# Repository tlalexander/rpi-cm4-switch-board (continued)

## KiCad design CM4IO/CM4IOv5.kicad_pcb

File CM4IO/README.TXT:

These files have been created in prerelease version 6 of KiCAD. If Version 6 isn't released yet then to use them you will need to download a nightly build of KiCAD. NB Nightly builds my have issues so please check the issue tracker. 

Some of the 3d models need to be downloaded form the following places and put into the CM4IO.3shapes directory some models are approximations.

https://datasheets.raspberrypi.org/cm4/CM4-step.zip
https://www.amphenol-icc.com/pci-express-1001878311200tlf.html
https://www.te.com/global-en/product-171826-4.html
https://www.molex.com/molex/products/part-detail/memory_card_socket/5033981892

The models provided in the 3dmodels directory are from various manufacturers including Diodes, Hirose, MTCONN,Toby, TRXCOM. Terms and conditions for the use of the models remain with the original manufacture.

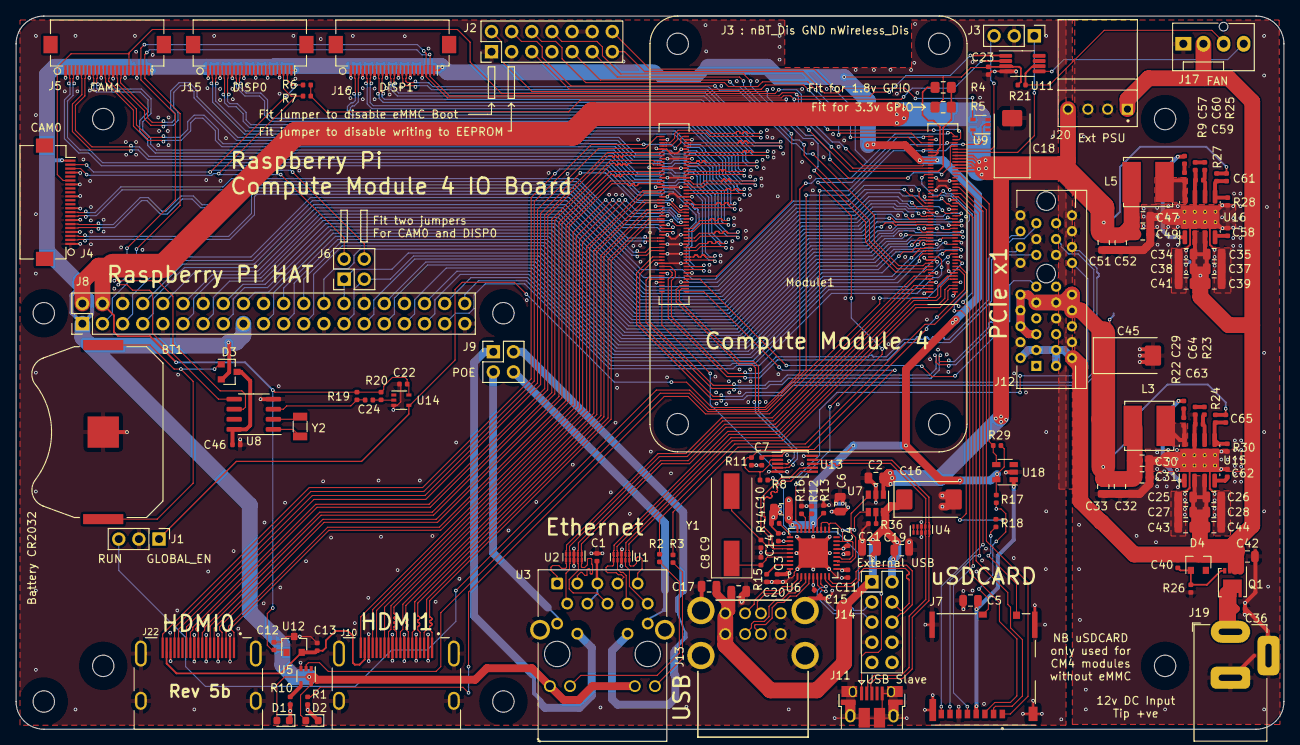
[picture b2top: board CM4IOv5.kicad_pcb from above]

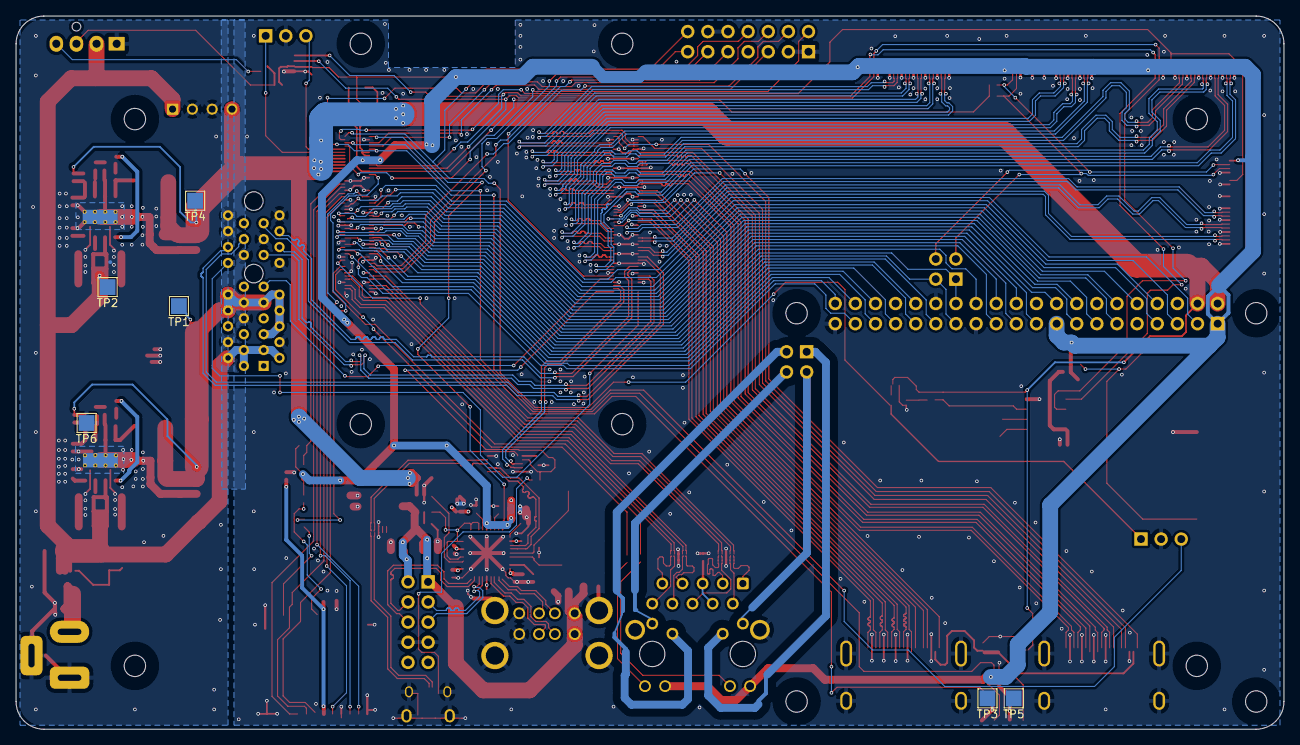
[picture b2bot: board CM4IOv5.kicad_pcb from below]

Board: 4 copper layers, 160.0 x 90.0 mm, 151 parts (6 on the bottom side), 204 nets.

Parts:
BT1: Battery_Cell; BatteryHolder_Keystone_3034_1x20mm
C1, C3, C4, C7, C11, C12, C13, C14, C15, C22, C23, C24, C29, C40, C46, C57, C58, C62: 100n; C_0402_1005Metric
C2, C5, C6, C10, C17, C19, C20, C21, C30, C31, C32, C33, C47, C49, C51, C52: 10u; C_0805_2012Metric
C8, C9: 27pF; C_0402_1005Metric
C16, C18, C45: 100uF; CP_EIA-7343-31_Kemet-D
C25, C26, C27, C28, C34, C35, C37, C38, C39, C41, C42, C43, C44: 10u 35v; C_0805_2012Metric
C36: 100n 100v; C_0402_1005Metric
C59, C61, C63, C65: nf; C_0402_1005Metric
C60, C64: 1.2nF; C_0402_1005Metric
D1: LED Red; LED_0603_1608Metric
D2: LED Green; LED_0603_1608Metric
D3: BAT54C-7-F; SOT-23
D4: MMBZ5242BLT3G; D_SOT-23_ANK
H1, H2, H3, H4, H5, H6, H7, H8: MountingHole; MountingHole_2.7mm_M2.5
J1, J3: Conn_01x03; PinHeader_1x03_P2.54mm_Vertical
J2: Conn_02x07_Odd_Even; PinHeader_2x07_P2.54mm_Vertical
J4, J5, J15, J16: Conn_01x22_Female; Hirose_FH12-22S-0.5SH_1x22-1MP_P0.50mm_Horizontal
J6, J9: THD-02-R; PinHeader_2x02_P2.54mm_Vertical
J7: Micro_SD_Card_Det; SDCARD_MOLEX_503398-1892
J8: THD-20-R; PinHeader_2x20_P2.54mm_Vertical
J10, J22: 690-019-298-412; EDAC 690-019-298-412
J11: USB_OTG; USB_Micro-B_EDAC_UCON00686
J12: 10018783-11200TLF; PCIex1-36
J13: 690-008-221-904; MOLEX_USB_67298-4090
J14: Conn_02x05_Odd_Even; PinHeader_2x05_P2.54mm_Vertical
J17: Molex 470531000; FanPinHeader_1x04_P2.54mm_Vertical
J19: Barrel_Jack; BarrelJack_Horizontal
J20: AMP171826-4; TE_171826-4
L3, L5: SRN6045TA-3R3Y; L_Bourns_SRN6045TA
Module1: ComputeModule4; Raspberry-Pi-4-Compute-Module
Q1: DMP3013SFV-7; Diodes_PowerDI3333-8
R1, R10: 1k; R_0402_1005Metric
R2, R3: 470R; R_0402_1005Metric
R4: nf; R_0805_2012Metric_Pad1.15x1.40mm_HandSolder
R5: 0R; R_0805_2012Metric_Pad1.15x1.40mm_HandSolder
R6, R7, R8, R11, R28: 2.2K 1%; R_0402_1005Metric
R9, R22: 10R; R_0402_1005Metric
R12, R13, R14, R16, R21: 36K 1%; R_0402_1005Metric
R15, R23, R26, R27, R29: 12K 1%; R_0402_1005Metric
R17, R18: nf; R_0402_1005Metric
R19, R20: 510K 1%; R_0402_1005Metric
R24: 47K 1%; R_0402_1005Metric
R25: 20K 1%; R_0402_1005Metric
R30, R36: 15K 1%; R_0402_1005Metric
TP1, TP2, TP3, TP4, TP5, TP6: TestPoint; TestPoint_Pad_2.0x2.0mm
U1, U2, U4: TPD4EUSB30; USON-10_2.5x1.0mm_P0.5mm
U3: MagJack-A70-112-331N126; TRJG0926HENL
U5, U9, U14: 74LVC1G07SE-7; SOT-353_SC-70-5
U6: USB2514B-I/M2; QFN-36-1EP_6x6mm_P0.5mm_EP3.7x3.7mm
U7: AP22653W6; SOT-23-6
U8: PCF85063AT/AAZ; SOIC-8_3.9x4.9mm_P1.27mm
U11: EMC2301-1-ACZL-TR; MSOP-8_3x3mm_P0.65mm
U12: RT9742SNGV; SOT-23
U13: FSUSB42MUX; MSOP-10_3x3mm_P0.5mm
U15, U16: AP64501SP-13; SOIC-8-1EP_3.9x4.9mm_P1.27mm_EP2.95x4.9mm_Mask2.71x3.4mm_Th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
U18: RT9742GGJ5; SOT-23-5
Y1: 24MHz; Crystal_SMD_HC49-SD
Y2: X32K768S301; Crystal_SMD_3215-2Pin_3.2x1.5mm

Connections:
/+3.3v: C3.1, C4.1, C6.1, C7.1, C10.1, C11.1, C14.1, C15.1, C23.1, D1.2 (A), D2.2 (A), D3.2, J4.22, J5.22, J8.1, J8.17, J15.22, J16.22, Module1.84 (+3.3v_(Output)), Module1.86 (+3.3v_(Output)), R5.1, R17.1, R21.2, R29.1, U3.15 (LEDG_A), U3.17 (LEDY_A), U5.5 (VCC), U6.5 (VDDA33), U6.10 (VDDA33), U6.15 (VDD33), U6.23 (VDD33), U6.27 (VBUS_DET), U6.29 (VDDA33), U6.36 (VDDA33), U11.3 (VDD), U13.1 (VCC), U18.5 (IN)
/+5v: C2.1, C12.1, C18.1, C22.1, C47.1, C49.1, C51.1, C52.1, C61.1, J8.2, J8.4, J20.4, L5.2, Module1.77 (+5v_(Input)), Module1.79 (+5v_(Input)), Module1.81 (+5v_(Input)), Module1.83 (+5v_(Input)), Module1.85 (+5v_(Input)), Module1.87 (+5v_(Input)), R19.2, R20.2, R27.1, TP4.1, U7.1 (IN), U9.5 (VCC), U12.1 (IN), U14.5 (VCC)
/+12v: C25.1, C26.1, C27.1, C28.1, C34.1, C35.1, C37.1, C38.1, C39.1, C40.1, C41.1, C42.1, C43.1, C44.1, D4.1 (K), J12.A2 (+12V), J12.A3 (+12V), J12.B1 (+12v), J12.B2 (+12v), J12.B3 (+12v), J17.2, J20.1, Q1.1 (S), Q1.2 (S), Q1.3 (S), TP2.1, U15.2 (VIN), U15.3 (EN), U16.2 (VIN), U16.3 (EN)
/CAM_GPIO: J4.17, J5.17, Module1.97 (Camera_GPIO)
/CM4_GPIO ( Ethernet, GPIO, SDCARD)/+1.8v: Module1.88 (+1.8v_(Output)), Module1.90 (+1.8v_(Output)), R4.1
/CM4_GPIO ( Ethernet, GPIO, SDCARD)/AIN0: J2.5, Module1.96 (AnalogIP0)
/CM4_GPIO ( Ethernet, GPIO, SDCARD)/AIN1: J2.6, Module1.94 (AnalogIP1)
/CM4_GPIO ( Ethernet, GPIO, SDCARD)/BT_nDis: J3.3, Module1.91 (BT_nDisable)
/CM4_GPIO ( Ethernet, GPIO, SDCARD)/EEPROM_nWP: J2.4, Module1.20 (EEPROM_nWP)
/CM4_GPIO ( Ethernet, GPIO, SDCARD)/ETH_LEDG: Module1.17 (Ethernet_nLED2(3.3v)), R2.2
/CM4_GPIO ( Ethernet, GPIO, SDCARD)/ETH_LEDY: Module1.15 (Ethernet_nLED3(3.3v)), R3.2
/CM4_GPIO ( Ethernet, GPIO, SDCARD)/GPIO2: J8.3, Module1.58 (GPIO2)
/CM4_GPIO ( Ethernet, GPIO, SDCARD)/GPIO3: J8.5, Module1.56 (GPIO3)
/CM4_GPIO ( Ethernet, GPIO, SDCARD)/GPIO4: J8.7, Module1.54 (GPIO4)
/CM4_GPIO ( Ethernet, GPIO, SDCARD)/GPIO5: J8.29, Module1.34 (GPIO5)
/CM4_GPIO ( Ethernet, GPIO, SDCARD)/GPIO6: J8.31, Module1.30 (GPIO6)
/CM4_GPIO ( Ethernet, GPIO, SDCARD)/GPIO7: J8.26, Module1.37 (GPIO7)
/CM4_GPIO ( Ethernet, GPIO, SDCARD)/GPIO8: J8.24, Module1.39 (GPIO8)
/CM4_GPIO ( Ethernet, GPIO, SDCARD)/GPIO9: J8.21, Module1.40 (GPIO9)
/CM4_GPIO ( Ethernet, GPIO, SDCARD)/GPIO10: J8.19, Module1.44 (GPIO10)
/CM4_GPIO ( Ethernet, GPIO, SDCARD)/GPIO11: J8.23, Module1.38 (GPIO11)
/CM4_GPIO ( Ethernet, GPIO, SDCARD)/GPIO12: J8.32, Module1.31 (GPIO12)
/CM4_GPIO ( Ethernet, GPIO, SDCARD)/GPIO13: J8.33, Module1.28 (GPIO13)
/CM4_GPIO ( Ethernet, GPIO, SDCARD)/GPIO14: J8.8, Module1.55 (GPIO14)
/CM4_GPIO ( Ethernet, GPIO, SDCARD)/GPIO15: J8.10, Module1.51 (GPIO15)
/CM4_GPIO ( Ethernet, GPIO, SDCARD)/GPIO16: J8.36, Module1.29 (GPIO16)
/CM4_GPIO ( Ethernet, GPIO, SDCARD)/GPIO17: J8.11, Module1.50 (GPIO17)
/CM4_GPIO ( Ethernet, GPIO, SDCARD)/GPIO18: J8.12, Module1.49 (GPIO18)
/CM4_GPIO ( Ethernet, GPIO, SDCARD)/GPIO19: J8.35, Module1.26 (GPIO19)
/CM4_GPIO ( Ethernet, GPIO, SDCARD)/GPIO20: J8.38, Module1.27 (GPIO20)
/CM4_GPIO ( Ethernet, GPIO, SDCARD)/GPIO21: J8.40, Module1.25 (GPIO21)
/CM4_GPIO ( Ethernet, GPIO, SDCARD)/GPIO22: J8.15, Module1.46 (GPIO22)
/CM4_GPIO ( Ethernet, GPIO, SDCARD)/GPIO23: J8.16, Module1.47 (GPIO23)
/CM4_GPIO ( Ethernet, GPIO, SDCARD)/GPIO24: J8.18, Module1.45 (GPIO24)
/CM4_GPIO ( Ethernet, GPIO, SDCARD)/GPIO25: J8.22, Module1.41 (GPIO25)
/CM4_GPIO ( Ethernet, GPIO, SDCARD)/GPIO26: J8.37, Module1.24 (GPIO26)
/CM4_GPIO ( Ethernet, GPIO, SDCARD)/GPIO27: J8.13, Module1.48 (GPIO27)
/CM4_GPIO ( Ethernet, GPIO, SDCARD)/RUN_PG: J1.3, Module1.92 (RUN_PG), U9.2
/CM4_GPIO ( Ethernet, GPIO, SDCARD)/Reserved: Module1.76 (Reserved), R18.1
/CM4_GPIO ( Ethernet, GPIO, SDCARD)/SD_CLK: J7.5 (CLK), Module1.57 (SD_CLK)
/CM4_GPIO ( Ethernet, GPIO, SDCARD)/SD_CMD: J7.3 (CMD), Module1.62 (SD_CMD)
/CM4_GPIO ( Ethernet, GPIO, SDCARD)/SD_DAT0: J7.7 (DAT0), Module1.63 (SD_DAT0)
/CM4_GPIO ( Ethernet, GPIO, SDCARD)/SD_DAT1: J7.8 (DAT1), Module1.67 (SD_DAT1)
/CM4_GPIO ( Ethernet, GPIO, SDCARD)/SD_DAT2: J7.1 (DAT2), Module1.69 (SD_DAT2)
/CM4_GPIO ( Ethernet, GPIO, SDCARD)/SD_DAT3: J7.2 (DAT3/CD), Module1.61 (SD_DAT3)
/CM4_GPIO ( Ethernet, GPIO, SDCARD)/SD_PWR: C5.1, J7.4 (VDD), U18.1 (OUT)
/CM4_GPIO ( Ethernet, GPIO, SDCARD)/SD_PWR_ON: Module1.75 (SD_PWR_ON), R29.2, U18.4 (EN)
/CM4_GPIO ( Ethernet, GPIO, SDCARD)/SYNC_IN: J2.8, Module1.16 (Ethernet_SYNC_IN(1.8v))
/CM4_GPIO ( Ethernet, GPIO, SDCARD)/SYNC_OUT: J2.9, Module1.18 (Ethernet_SYNC_OUT(1.8v))
/CM4_GPIO ( Ethernet, GPIO, SDCARD)/TR0_TAP: J9.3, U3.11 (VC1)
/CM4_GPIO ( Ethernet, GPIO, SDCARD)/TR1_TAP: J9.1, U3.12 (VC2)
/CM4_GPIO ( Ethernet, GPIO, SDCARD)/TR2_TAP: J9.2, U3.13 (VC3)
/CM4_GPIO ( Ethernet, GPIO, SDCARD)/TR3_TAP: J9.4, U3.14 (VC4)
/CM4_GPIO ( Ethernet, GPIO, SDCARD)/TRD0_N: Module1.10 (Ethernet_Pair0_N), U2.4 (D2+), U2.7, U3.2 (TRD0-)
/CM4_GPIO ( Ethernet, GPIO, SDCARD)/TRD0_P: Module1.12 (Ethernet_Pair0_P), U2.5 (D2-), U2.6, U3.1 (TRD0+)
/CM4_GPIO ( Ethernet, GPIO, SDCARD)/TRD1_N: Module1.6 (Ethernet_Pair1_N), U2.2 (D1-), U2.9, U3.6 (TRD1-)
/CM4_GPIO ( Ethernet, GPIO, SDCARD)/TRD1_P: Module1.4 (Ethernet_Pair1_P), U2.1 (D1+), U2.10, U3.3 (TRD1+)
/CM4_GPIO ( Ethernet, GPIO, SDCARD)/TRD2_N: Module1.9 (Ethernet_Pair2_N), U1.4 (D2+), U1.7, U3.8 (TRD2-)
/CM4_GPIO ( Ethernet, GPIO, SDCARD)/TRD2_P: Module1.11 (Ethernet_Pair2_P), U1.5 (D2-), U1.6, U3.7 (TRD2+)
/CM4_GPIO ( Ethernet, GPIO, SDCARD)/TRD3_N: Module1.5 (Ethernet_Pair3_N), U1.2 (D1-), U1.9, U3.10 (TRD3-)
/CM4_GPIO ( Ethernet, GPIO, SDCARD)/TRD3_P: Module1.3 (Ethernet_Pair3_P), U1.1 (D1+), U1.10, U3.9 (TRD3+)
/CM4_GPIO ( Ethernet, GPIO, SDCARD)/WL_nDis: J3.1, Module1.89 (WL_nDisable)
/CM4_GPIO ( Ethernet, GPIO, SDCARD)/nPWR_LED: Module1.95 (nPI_LED_PWR), U5.2
/CM4_GPIO ( Ethernet, GPIO, SDCARD)/nRPIBOOT: J2.2, Module1.93 (nRPIBOOT)
/CM4_HighSpeed/CAM0_C_N: J4.8, Module1.140 (CAM0_C_N)
/CM4_HighSpeed/CAM0_C_P: J4.9, Module1.142 (CAM0_C_P)
/CM4_HighSpeed/CAM0_D0_N: J4.2, Module1.128 (CAM0_D0_N)
/CM4_HighSpeed/CAM0_D0_P: J4.3, Module1.130 (CAM0_D0_P)
/CM4_HighSpeed/CAM0_D1_N: J4.5, Module1.134 (CAM0_D1_N)
/CM4_HighSpeed/CAM0_D1_P: J4.6, Module1.136 (CAM0_D1_P)
/CM4_HighSpeed/CAM1_C_N: J5.8, Module1.127 (CAM1_C_N)
/CM4_HighSpeed/CAM1_C_P: J5.9, Module1.129 (CAM1_C_P)
/CM4_HighSpeed/CAM1_D0_N: J5.2, Module1.115 (CAM1_D0_N)
/CM4_HighSpeed/CAM1_D0_P: J5.3, Module1.117 (CAM1_D0_P)
/CM4_HighSpeed/CAM1_D1_N: J5.5, Module1.121 (CAM1_D1_N)
/CM4_HighSpeed/CAM1_D1_P: J5.6, Module1.123 (CAM1_D1_P)
/CM4_HighSpeed/CAM1_D2_N: J5.11, Module1.133 (CAM1_D2_N)
/CM4_HighSpeed/CAM1_D2_P: J5.12, Module1.135 (CAM1_D2_P)
/CM4_HighSpeed/CAM1_D3_N: J5.14, Module1.139 (CAM1_D3_N)
/CM4_HighSpeed/CAM1_D3_P: J5.15, Module1.141 (CAM1_D3_P)
/CM4_HighSpeed/DSI0_C_N: J15.8, Module1.169 (DSI0_C_N)
/CM4_HighSpeed/DSI0_C_P: J15.9, Module1.171 (DSI0_C_P)
/CM4_HighSpeed/DSI0_D0_N: J15.2, Module1.157 (DSI0_D0_N)
/CM4_HighSpeed/DSI0_D0_P: J15.3, Module1.159 (DSI0_D0_P)
/CM4_HighSpeed/DSI0_D1_N: J15.5, Module1.163 (DSI0_D1_N)
/CM4_HighSpeed/DSI0_D1_P: J15.6, Module1.165 (DSI0_D1_P)
/CM4_HighSpeed/DSI1_C_N: J16.8, Module1.187 (DSI1_C_N)
/CM4_HighSpeed/DSI1_C_P: J16.9, Module1.189 (DSI1_C_P)
/CM4_HighSpeed/DSI1_D0_N: J16.2, Module1.175 (DSI1_D0_N)
/CM4_HighSpeed/DSI1_D0_P: J16.3, Module1.177 (DSI1_D0_P)
/CM4_HighSpeed/DSI1_D1_N: J16.5, Module1.181 (DSI1_D1_N)
/CM4_HighSpeed/DSI1_D1_P: J16.6, Module1.183 (DSI1_D1_P)
/CM4_HighSpeed/DSI1_D2_N: J16.11, Module1.193 (DSI1_D2_N)
/CM4_HighSpeed/DSI1_D2_P: J16.12, Module1.195 (DSI1_D2_P)
/CM4_HighSpeed/DSI1_D3_N: J16.14, Module1.194 (DSI1_D3_N)
/CM4_HighSpeed/DSI1_D3_P: J16.15, Module1.196 (DSI1_D3_P)
/CM4_HighSpeed/HDMI0_CEC: J22.13 (CEC), Module1.151 (HDMI0_CEC)
/CM4_HighSpeed/HDMI0_CK_N: J22.12 (CK-), Module1.190 (HDMI0_CLK_N)
/CM4_HighSpeed/HDMI0_CK_P: J22.10 (CK+), Module1.188 (HDMI0_CLK_P)
/CM4_HighSpeed/HDMI0_D0_N: J22.9 (D0-), Module1.184 (HDMI0_TX0_N)
/CM4_HighSpeed/HDMI0_D0_P: J22.7 (D0+), Module1.182 (HDMI0_TX0_P)
/CM4_HighSpeed/HDMI0_D1_N: J22.6 (D1-), Module1.178 (HDMI0_TX1_N)
/CM4_HighSpeed/HDMI0_D1_P: J22.4 (D1+), Module1.176 (HDMI0_TX1_P)
/CM4_HighSpeed/HDMI0_D2_N: J22.3 (D2-), Module1.172 (HDMI0_TX2_N)
/CM4_HighSpeed/HDMI0_D2_P: J22.1 (D2+), Module1.170 (HDMI0_TX2_P)
/CM4_HighSpeed/HDMI0_HOTPLUG: J22.19 (HPD/HEAC-), Module1.153 (HDMI0_HOTPLUG)
/CM4_HighSpeed/HDMI0_SCL: J22.15 (SCL), Module1.200 (HDMI0_SCL)
/CM4_HighSpeed/HDMI0_SDA: J22.16 (SDA), Module1.199 (HDMI0_SDA)
/CM4_HighSpeed/HDMI1_CEC: J10.13 (CEC), Module1.149 (HDMI1_CEC)
/CM4_HighSpeed/HDMI1_CK_N: J10.12 (CK-), Module1.166 (HDMI1_CLK_N)
/CM4_HighSpeed/HDMI1_CK_P: J10.10 (CK+), Module1.164 (HDMI1_CLK_P)
/CM4_HighSpeed/HDMI1_D0_N: J10.9 (D0-), Module1.160 (HDMI1_TX0_N)
/CM4_HighSpeed/HDMI1_D0_P: J10.7 (D0+), Module1.158 (HDMI1_TX0_P)
/CM4_HighSpeed/HDMI1_D1_N: J10.6 (D1-), Module1.154 (HDMI1_TX1_N)
/CM4_HighSpeed/HDMI1_D1_P: J10.4 (D1+), Module1.152 (HDMI1_TX1_P)
/CM4_HighSpeed/HDMI1_D2_N: J10.3 (D2-), Module1.148 (HDMI1_TX2_N)
/CM4_HighSpeed/HDMI1_D2_P: J10.1 (D2+), Module1.146 (HDMI1_TX2_P)
/CM4_HighSpeed/HDMI1_HOTPLUG: J10.19 (HPD/HEAC-), Module1.143 (HDMI1_HOTPLUG)
/CM4_HighSpeed/HDMI1_SCL: J10.15 (SCL), Module1.147 (HDMI1_SCL)
/CM4_HighSpeed/HDMI1_SDA: J10.16 (SDA), Module1.145 (HDMI1_SDA)
/CM4_HighSpeed/HDMI_5v: C13.1, J10.18 (+5V), J22.18 (+5V), U12.2 (OUT)
/CM4_HighSpeed/SCL1: J4.20, J6.2, J15.20, R7.2
/CM4_HighSpeed/SDA1: J4.21, J6.4, J15.21, R6.2
/GLOBAL_EN: J1.1, J2.14, Module1.99 (Global_EN), U14.4
/GPIO_VREF: Module1.78 (GPIO_VREF(1.8v/3.3v_Input)), R4.2, R5.2, R6.1, R7.1
/ID_SC: J6.1, J8.28, Module1.35 (ID_SC)
/ID_SD: J6.3, J8.27, Module1.36 (ID_SD)
/PCIE_CLK_N: J12.A14 (REFCLK-), Module1.112 (PCIe_CLK_N)
/PCIE_CLK_P: J12.A13 (REFCLK+), Module1.110 (PCIe_CLK_P)
/PCIE_CLK_nREQ: J12.B12 (nCLKREQ), Module1.102 (PCIe_CLK_nREQ)
/PCIE_RX_N: J12.A16 (PERP0), Module1.118 (PCIe_RX_N)
/PCIE_RX_P: J12.A17 (PERN0), Module1.116 (PCIe_RX_P)
/PCIE_TX_N: J12.B14 (PETP0), Module1.124 (PCIe_TX_N)
/PCIE_TX_P: J12.B15 (PETN0), Module1.122 (PCIe_TX_P)
/PCIE_nRST: J12.A11 (nPERST), Module1.109 (PCIe_nRST)
/PCIe-connector/+3.3v: C30.1, C31.1, C32.1, C33.1, C45.1, C65.1, J12.A5 (TCK), J12.A6 (TDI), J12.A8 (TMS), J12.A9 (+3.3V), J12.A10 (+3.3V), J12.B8 (+3.3v), J12.B9 (nTRST), J12.B10 (+3.3vAUX), L3.2, R24.1, TP1.1
/RTC , Wakeup, FAN/nRTC_INT: C24.2, R19.1, U8.3 (~INT~)
/SCL0: J5.20, J16.20, Module1.80 (SCL0), U8.6 (SCL), U11.2 (SCL)
/SDA0: J5.21, J16.21, Module1.82 (SDA0), U8.5 (SDA), U11.1 (SDA)
/TV_OUT: J2.11, Module1.111 (VDAC_COMP)
/USB2-HUB/HD1_N: J13.2 (D-`), U6.1 (USBDM_DN1/PRT_DIS_M1)
/USB2-HUB/HD1_P: J13.3 (D+`), U6.2 (USBDP_DN1/PRT_DIS_P1)
/USB2-HUB/HD2_N: J13.6 (D-), U6.3 (USBDM_DN2/PRT_DIS_M2)
/USB2-HUB/HD2_P: J13.7 (D+), U6.4 (USBDP_DN2/PRT_DIS_P2)
/USB2-HUB/HD3_N: J14.3, U6.6 (USBDM_DN3/PRT_DIS_M3)
/USB2-HUB/HD3_P: J14.5, U6.7 (USBDP_DN3/PRT_DIS_P3)
/USB2-HUB/HD4_N: J14.4, U6.8 (USBDM_DN4/PRT_DIS_M4)
/USB2-HUB/HD4_P: J14.6, U6.9 (USBDP_DN4/PRT_DIS_P4)
/USB2-HUB/PWR1: U6.12 (PRTPWR1/BC_EN1), U7.3 (EN)
/USB2-HUB/USBD_N: J11.2 (D-), U4.4 (D2+), U4.7, U13.8 (HSD1_M)
/USB2-HUB/USBD_P: J11.3 (D+), U4.5 (D2-), U4.6, U13.9 (HSD1_P)
/USB2-HUB/USBH_N: U6.30 (USBDM_UP), U13.6 (HSD0_M)
/USB2-HUB/USBH_P: U6.31 (USBDP_UP), U13.7 (HSD0_P)
/USB2-HUB/VBUS: C16.1, C17.1, C19.1, C20.1, C21.1, J13.1 (VBUS`), J13.5 (VBUS), J14.1, J14.2, U7.6 (OUT)
/USB2-HUB/nOCS1: U6.13 (OCS_N1), U6.17 (OCS_N2), U6.19 (OCS_N3), U6.21 (OCS_N4), U7.4 (nFault)
/USB2_N: Module1.103 (USB2_N), U13.4 (D_N)
/USB2_P: Module1.105 (USB2_P), U13.3 (D_P)
/USBOTG: Module1.101 (USB_OTG_ID), R8.2, R11.1, U13.2 (SEL)
/nEXTRST: Module1.100 (nEXTRST), U6.26 (RESET_N)
GND: BT1.2 (-), C1.2, C2.2, C3.2, C4.2, C5.2, C6.2, C7.2, C8.2, C9.2, C10.2, C11.2, C12.2, C13.2, C14.2, C15.2, C16.2, C17.2, C18.2, C19.2, C20.2, C21.2, C22.2, C23.2, C25.2, C26.2, C27.2, C28.2, C30.2, C31.2, C32.2, C33.2, C34.2, C35.2, C36.2, C37.2, C38.2, C39.2, C41.2, C42.2, C43.2, C44.2, C45.2, C46.2, C47.2, C49.2, C51.2, C52.2, C58.2, C59.2, C60.2, C62.2, C63.2, C64.2, J1.2, J2.1, J2.3, J2.7, J2.10, J2.12, J3.2, J4.1, J4.4, J4.7, J4.10, J4.13, J4.16, J4.19, J5.1, J5.4, J5.7, J5.10, J5.13, J5.16, J5.19, J7.6 (VSS), J7.11 (SHIELD), J8.6, J8.9, J8.14, J8.20, J8.25, J8.30, J8.34, J8.39, J10.2 (D2S), J10.5 (D1S), J10.8 (D0S), J10.11 (CKS), J10.17 (GND), J10.SH1 (SH), J10.SH2 (SH), J10.SH3 (SH), J10.SH4 (SH), J11.5 (GND), J11.6 (Shield), J12.A4 (GND), J12.A12 (GND), J12.A15 (GND), J12.A18 (GND), J12.B4 (GND), J12.B7 (GND), J12.B13 (GND), J12.B16 (GND), J12.B18 (GND), J13.4 (GND`), J13.8 (GND), J13.MT1, J13.MT2, J13.MT3, J13.MT4, J14.7, J14.8, J15.1, J15.4, J15.7, J15.10, J15.13, J15.16, J15.19, J16.1, J16.4, J16.7, J16.10, J16.13, J16.16, J16.19, J17.1, J19.2, J19.3, J20.2, J20.3, J22.2 (D2S), J22.5 (D1S), J22.8 (D0S), J22.11 (CKS), J22.17 (GND), J22.SH1 (SH), J22.SH2 (SH), J22.SH3 (SH), J22.SH4 (SH), Module1.1 (GND), Module1.2 (GND), Module1.7 (GND), Module1.8 (GND), Module1.13 (GND), Module1.14 (GND), Module1.22 (GND), Module1.23 (GND), Module1.32 (GND), Module1.33 (GND), Module1.42 (GND), Module1.43 (GND), Module1.52 (GND), Module1.53 (GND), Module1.59 (GND), Module1.60 (GND), Module1.65 (GND), Module1.66 (GND), Module1.71 (GND), Module1.74 (GND), Module1.98 (GND), Module1.107 (GND), Module1.108 (GND), Module1.113 (GND), Module1.114 (GND), Module1.119 (GND), Module1.120 (GND), Module1.125 (GND), Module1.126 (GND), Module1.131 (GND), Module1.132 (GND), Module1.137 (GND), Module1.138 (GND), Module1.144 (GND), Module1.150 (GND), Module1.155 (GND), Module1.156 (GND), Module1.161 (GND), Module1.162 (GND), Module1.167 (GND), Module1.168 (GND), Module1.173 (GND), Module1.174 (GND), Module1.179 (GND), Module1.180 (GND), Module1.185 (GND), Module1.186 (GND), Module1.191 (GND), Module1.192 (GND), Module1.197 (GND), Module1.198 (GND), R11.2, R12.2, R13.2, R14.2, R15.1, R16.2, R26.2, R28.2, R30.2, R36.2, TP6.1, U1.3 (GND), U1.8 (GND), U2.3 (GND), U2.8 (GND), U3.19 (SHIELD), U3.20 (SHIELD), U4.3 (GND), U4.8 (GND), U5.3 (GND), U6.37 (VSS), U7.2 (GND), U8.4 (VSS), U9.3 (GND), U11.4 (GND), U12.3 (GND), U13.5 (GND), U13.10 (nOE), U14.3 (GND), U15.7 (GND), U15.9 (EP), U16.7 (GND), U16.9 (EP), U18.2 (GND)
unnamed: BT1.1 (+), D3.1
unnamed: C1.1, U3.4 (CT), U3.5 (CT)
unnamed: C8.1, U6.33 (XTALIN/CLKIN), Y1.1
unnamed: C9.1, U6.32 (XTALOUT), Y1.2
unnamed: C24.1, R20.1, U14.2
unnamed: C29.1, R22.2
unnamed: C29.2, U15.1 (BST)
unnamed: C36.1, J19.1, Q1.5 (D)
unnamed: C40.2, D4.2 (A), Q1.4 (G), R26.1
unnamed: C46.1, D3.3, U8.8 (VDD)
unnamed: C57.1, R9.2
unnamed: C57.2, U16.1 (BST)
unnamed: C58.1, U16.4 (SS)
unnamed: C59.1, R25.1, U16.6 (COMP)
unnamed: C60.1, R25.2
unnamed: C61.2, R27.2, R28.1, U16.5 (FB)
unnamed: C62.1, U15.4 (SS)
unnamed: C63.1, R23.1, U15.6 (COMP)
unnamed: C64.1, R23.2
unnamed: C65.2, R24.2, R30.1, U15.5 (FB)
unnamed: D1.1 (K), R10.1, TP5.1
unnamed: D2.1 (K), R1.1, TP3.1
unnamed: J2.13, U9.4
unnamed: J7.9 (DET_B), R18.2
unnamed: J7.10 (DET_A), R17.2
unnamed: J11.1 (VBUS), R8.1
unnamed: J17.3, R21.1, U11.6 (TACH)
unnamed: J17.4, U11.5 (PWM)
unnamed: L3.1, R22.1, U15.8 (SW)
unnamed: L5.1, R9.1, U16.8 (SW)
unnamed: Module1.21 (PI_nLED_Activity), R1.2
unnamed: R2.1, U3.16 (LEDG_K)
unnamed: R3.1, U3.18 (LEDY_K)
unnamed: R10.2, U5.4
unnamed: R12.1, U6.24 (SCL/SMBCLK/CFG_SEL0)
unnamed: R13.1, U6.22 (SDA/SMBDATA/NON_REM1)
unnamed: R14.1, U6.28 (SUSP_IND/LOCAL_PWR/NON_REM0)
unnamed: R15.2, U6.35 (RBIAS)
unnamed: R16.1, U6.25 (HS_IND/CFG_SEL1)
unnamed: R36.1, U7.5 (ILIM)
unnamed: U4.1 (D1+), U4.10
unnamed: U4.2 (D1-), U4.9
unnamed: U8.1 (OSCI), Y2.2
unnamed: U8.2 (OSCO), Y2.1

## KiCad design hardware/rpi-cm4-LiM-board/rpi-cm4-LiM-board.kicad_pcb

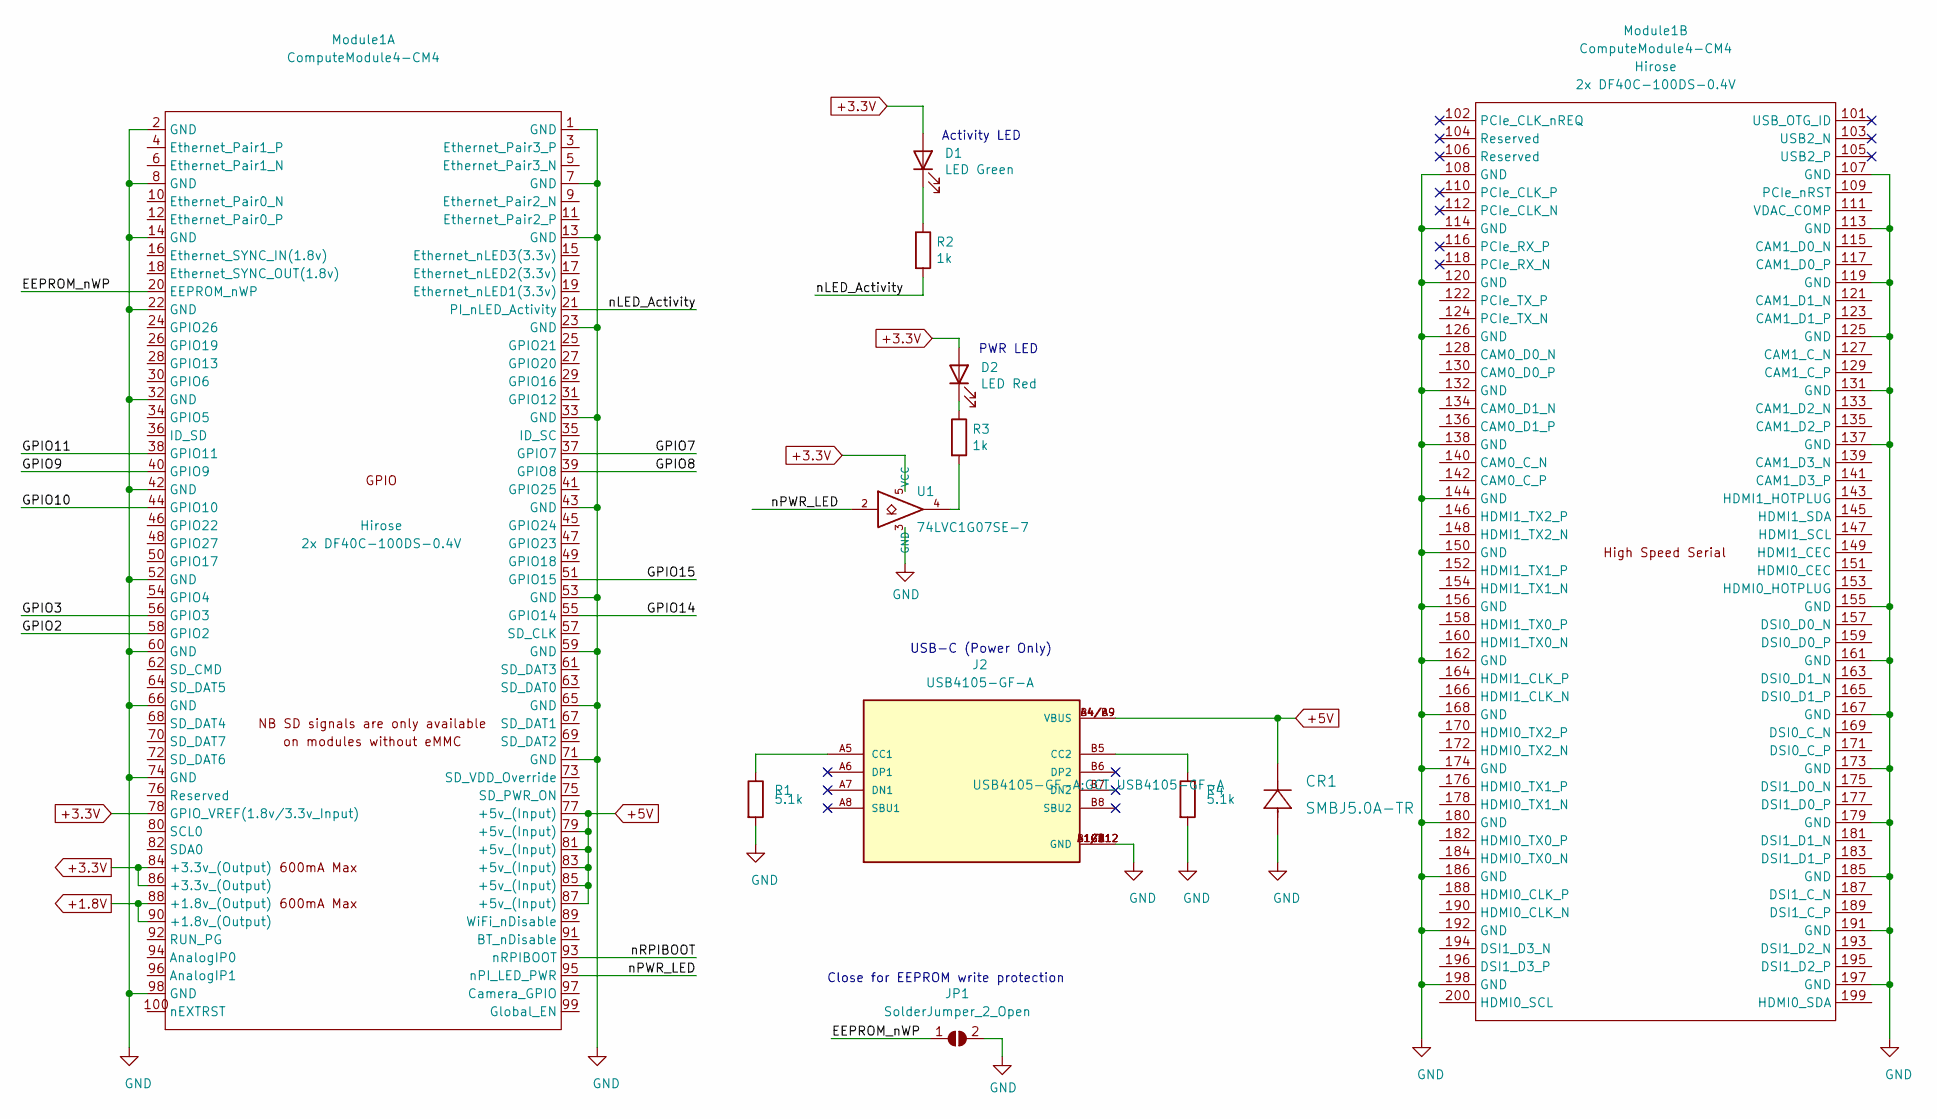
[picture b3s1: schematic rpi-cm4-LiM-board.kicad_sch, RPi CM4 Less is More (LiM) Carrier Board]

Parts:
CR1: SMBJ5.0A-TR; MPN SMBJ5.0A-TR; Digi-Key_PN 497-3144-1-ND
D1: LED Green; LED_0603_1608Metric; Part Description Green 572nm LED Indication - Discrete 2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; Digi-Key_PN 160-1478-1-ND
D2: LED Red; LED_0603_1608Metric; Part Description Red 620nm LED Indication - Discrete 2.2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; Digi-Key_PN 160-1479-1-ND
J2: USB4105-GF-A; GCT_USB4105-GF-A; MPN USB4105-GF-A; Digi-Key_PN 2073-USB4105-GF-ACT-ND
JP1: SolderJumper_2_Open; SolderJumper-2_P1.3mm_Open_RoundedPad1.0x1.5mm
Module1: ComputeModule4-CM4; Raspberry-Pi-4-Compute-Module; MPN 2x DF40C-100DS-0.4V; Digi-Key_PN 2x H11615CT-ND
R1, R4: 5.1k; R_0603_1608Metric_Pad0.98x0.95mm_HandSolder; MPN RC0603FR-075K1L; Digi-Key_PN 311-5.10KHRCT-ND
R2, R3: 1k; R_0603_1608Metric_Pad0.98x0.95mm_HandSolder; MPN RC0603FR-071KL; Digi-Key_PN 311-1.00KHRCT-ND
U1: 74LVC1G07SE-7; SOT-353_SC-70-5; Part Description Buffer, Non-Inverting 1 Element 1 Bit p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; Digi-Key_PN 74LVC1G07SE-7DICT-ND

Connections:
+1.8V: Module1.88 (+1.8v_(Output)), Module1.90 (+1.8v_(Output))
+3.3V: D1.2 (A), D2.2 (A), Module1.78 (GPIO_VREF(1.8v/3.3v_Input)), Module1.84 (+3.3v_(Output)), Module1.86 (+3.3v_(Output)), U1.5 (VCC)
+5V: CR1.1, J2.A4/B9 (VBUS), J2.B4/A9 (VBUS), Module1.77 (+5v_(Input)), Module1.79 (+5v_(Input)), Module1.81 (+5v_(Input)), Module1.83 (+5v_(Input)), Module1.85 (+5v_(Input)), Module1.87 (+5v_(Input))
/CM4 GPIO/EEPROM_nWP: JP1.1 (A), Module1.20 (EEPROM_nWP)
/CM4 GPIO/GPIO2: Module1.58 (GPIO2)
/CM4 GPIO/GPIO3: Module1.56 (GPIO3)
/CM4 GPIO/GPIO7: Module1.37 (GPIO7)
/CM4 GPIO/GPIO8: Module1.39 (GPIO8)
/CM4 GPIO/GPIO9: Module1.40 (GPIO9)
/CM4 GPIO/GPIO10: Module1.44 (GPIO10)
/CM4 GPIO/GPIO11: Module1.38 (GPIO11)
/CM4 GPIO/GPIO14: Module1.55 (GPIO14)
/CM4 GPIO/GPIO15: Module1.51 (GPIO15)
/CM4 GPIO/nLED_Activity: Module1.21 (PI_nLED_Activity), R2.2
/CM4 GPIO/nPWR_LED: Module1.95 (nPI_LED_PWR), U1.2
/CM4 GPIO/nRPIBOOT: Module1.93 (nRPIBOOT)
GND: CR1.2, J2.A1/B12 (GND), J2.B1/A12 (GND), J2.G1 (GND), J2.G2 (GND), J2.G3 (GND), J2.G4 (GND), JP1.2 (B), Module1.1 (GND), Module1.2 (GND), Module1.7 (GND), Module1.8 (GND), Module1.13 (GND), Module1.14 (GND), Module1.22 (GND), Module1.23 (GND), Module1.32 (GND), Module1.33 (GND), Module1.42 (GND), Module1.43 (GND), Module1.52 (GND), Module1.53 (GND), Module1.59 (GND), Module1.60 (GND), Module1.65 (GND), Module1.66 (GND), Module1.71 (GND), Module1.74 (GND), Module1.98 (GND), Module1.107 (GND), Module1.108 (GND), Module1.113 (GND), Module1.114 (GND), Module1.119 (GND), Module1.120 (GND), Module1.125 (GND), Module1.126 (GND), Module1.131 (GND), Module1.132 (GND), Module1.137 (GND), Module1.138 (GND), Module1.144 (GND), Module1.150 (GND), Module1.155 (GND), Module1.156 (GND), Module1.161 (GND), Module1.162 (GND), Module1.167 (GND), Module1.168 (GND), Module1.173 (GND), Module1.174 (GND), Module1.179 (GND), Module1.180 (GND), Module1.185 (GND), Module1.186 (GND), Module1.191 (GND), Module1.192 (GND), Module1.197 (GND), Module1.198 (GND), R1.2, R4.2, U1.3 (GND)
unnamed: D1.1 (K), R2.1
unnamed 18: D2.1 (K), R3.1; also elsewhere on the board
unnamed: J2.A5 (CC1), R1.1
unnamed: J2.B5 (CC2), R4.1
unnamed 21: R3.2, U1.4; also elsewhere on the board

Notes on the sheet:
Activity LED
PWR LED
USB-C (Power Only)
Close for EEPROM write protection

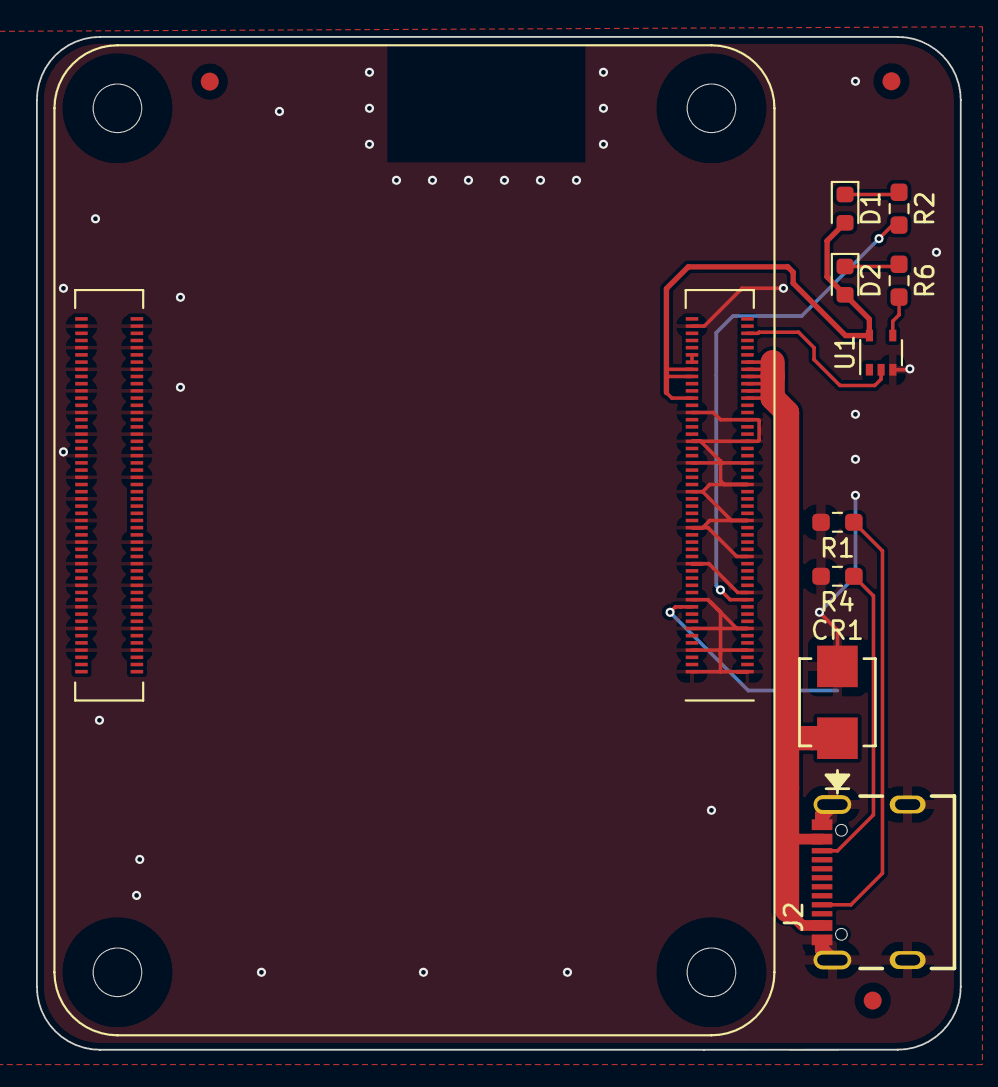
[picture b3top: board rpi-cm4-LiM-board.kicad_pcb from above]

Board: 2 copper layers, 51.3 x 56.3 mm, 11 parts (1 on the bottom side), 12 nets.

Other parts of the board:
R6: 1k; R_0603_1608Metric_Pad0.98x0.95mm_HandSolder

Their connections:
unnamed 18: R6.1; also elsewhere on the board
unnamed 21: R6.2; also elsewhere on the board

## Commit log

2021-06-08 updated to LiM board
2021-06-08 Update README.md
    started edits and updates to LiM board
2021-06-08 Update README.md
    Updated picture URL and text
2021-06-13 added new pictures and updated README.md
2021-06-13 upadte README.md
2021-06-13 upadted link in README.md
2021-06-13 upadted Shawn's info in README.md
2021-06-13 changes to README.md
2021-06-13 added blog URL to README.md
2021-06-13 changed typos in README.md
2021-06-13 fixed typos in README.md
2021-06-14 added table in README.md
2021-06-14 updaed table in README.md
2021-06-14 Update README.md
    updating unicode emoticons codes
2021-06-14 Create CNAME
2021-06-14 Set theme jekyll-theme-slate
2021-06-14 Update README.md
    updated emoticons unicodes for all items
2021-06-14 Update README.md
    fixed cross mark unicode
2021-06-14 Add files via upload
    Added favicon
2021-06-14 created default.html in _layouts
2021-06-14 changed favicon to png
2021-06-14 Update default.html
    updated default.htm
2021-06-14 reverted back some changes
2021-06-14 added About section to README.md
2021-06-14 Update README.md
    Formatting update in README.md
2021-06-15 added 3D images of LiM Carrier Board
2021-06-15 fixed URL typo in README.md
2021-06-15 fixed another URL typo in README.md
2021-06-15 added seperate table for 3D renders in README.md
2021-06-15 updatred git stats box in README.md
2021-06-15 commented out line in README.md
2021-06-28 added google adsense code to _includes/google_adsense.html
2021-06-28 modified _config.yml to include google_adsense.html
2021-06-28 reverted changes
2021-06-29 added Google Adsense snippet to blog posts
2021-06-30 added google analytics
2021-06-30 fixed google analytics
2021-06-30 fixed google analytics script in header
2021-07-05 attempt to make index.md relative
2021-07-05 added git ignore file
2021-07-05 test index.md
2021-07-05 reverted test in index.md
2021-07-15 Create FUNDING.yml
    added github sponsorship button
2021-07-15 Update FUNDING.yml
    added github username
2021-07-15 Update FUNDING.yml
    updated funding list
2021-07-15 added sponsorship button
2021-07-15 updated css and defaulthtml
2021-07-15 reverted changes in css and defaulthtml
2021-07-16 updated README and added seperate LiM Carrier Board page
2021-07-16 additional edits
2021-07-16 added youtube video
2021-07-16 Update README.md
    updated video link
2021-07-16 Update README.md
    minor edit
2021-07-16 Add files via upload
    Added cropped video
2021-07-16 Update README.md
    video link modification
2021-07-16 Update README.md
    changed video to gif
2021-07-16 Delete InVideo___Project_ID__531pprenderfs_1626439577092.mp4
    video removed
2021-07-16 Update README.md
    video link removed
2021-07-16 Delete README - Copy.md
    deleted file
2021-07-16 Update LiM_Board.md
    Updated with LiM pics and links plus video
2021-07-16 added images
2021-07-16 Update LiM_Board.md
    fixed video link
2021-07-16 resized images
2021-07-16 resized images 25%
2021-07-17 Update LiM_Board.md
    edited video link
2021-07-19 added design credit
2021-07-19 fixed typo in credit link
2021-07-19 fixed speling mistake in Readme
2021-07-19 added google analytics to config
2021-07-19 fixed spelling mistake in Readme
2021-07-23 Initial commit of cm4 switch board
2021-07-23 Add image to readme.
2021-07-23 Update readme. Add switch chip information.
2021-07-26 Differential routing completed/roughed out. Schematic cleanup. More work to do on chip power pins.
2021-09-06 Updated schematic symbol and footprint for ethernet chip, More work TBD
2021-09-07 Updated KSZ9567 symbol. Went through full pin list and fixed a few missing pin definitions.
